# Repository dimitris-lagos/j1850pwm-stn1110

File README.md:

# j1850pwm-stn1110
OBD 2 interface with atmega328 and STN1110. Output on 16x2 LCD Screen. Implements j1850 pwm protocol.
ATMega328P fuses:
L: 0xFF
H: 0xDD
E: 0xF8
LB: 0xFD

Cad 3D Model Schematic

Prototype connected to ECU Emulator

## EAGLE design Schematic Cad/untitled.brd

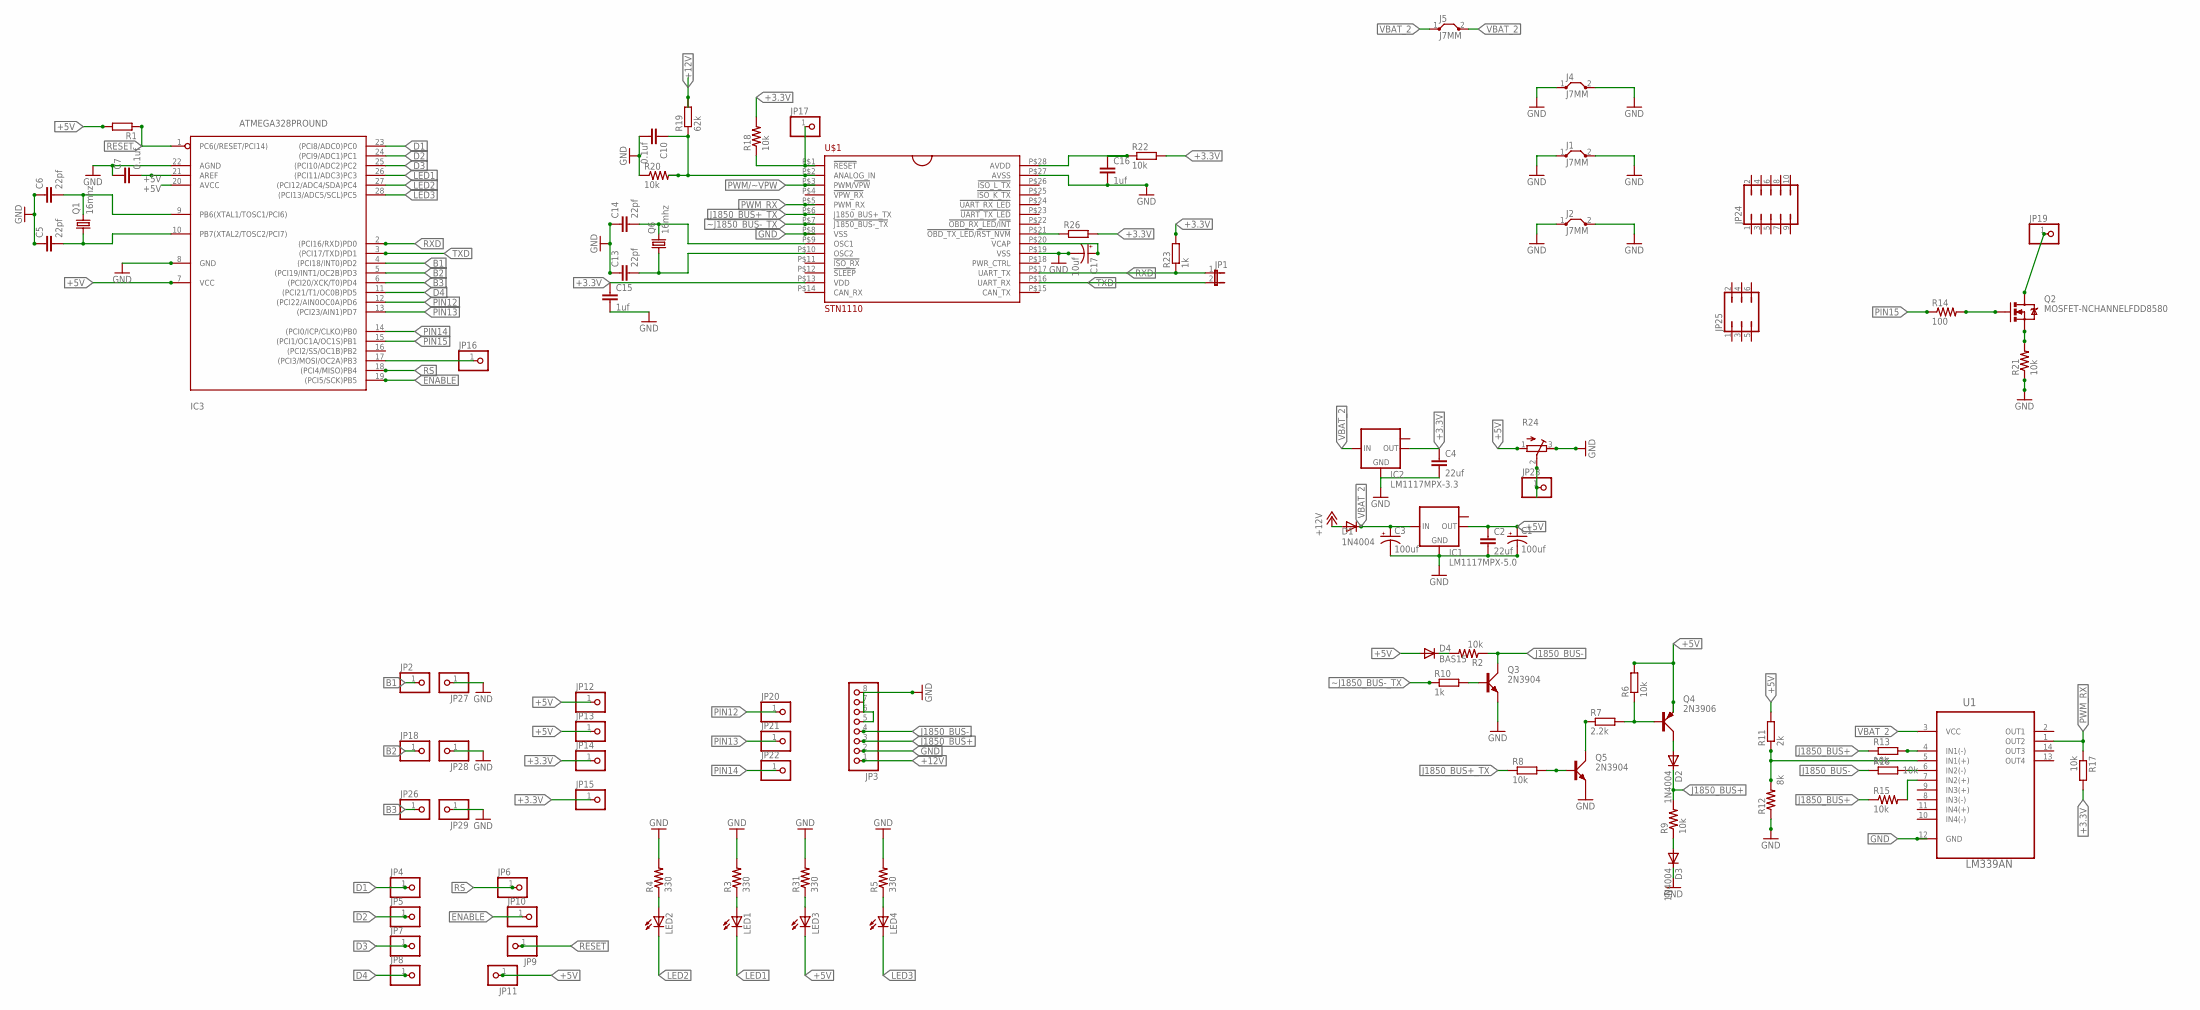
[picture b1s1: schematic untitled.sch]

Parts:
C1, C3: 100uf; CPOL-RADIAL-10UF-25V-KIT
C2, C4: 22uf; C025-025X050
C5, C6, C13, C14: 22pf; CAP-PTH-SMALL
C7: 0.1uf; C5B4.5
C10: 0.1uf; C025-025X050
C15, C16: 1uf; C025-025X050
C17: 10uf; CPOL-RADIAL-10UF-25V
D1, D2, D3: 1N4004; DO41-10
D4: BAS15; DO34-7
IC1: LM1117MPX-5.0; SOT223
IC2: LM1117MPX-3.3; SOT223
IC3: ATMEGA328PROUND; DIL28-3-ROUND
J1, J2, J4, J5: J7MM; 07
JP1: JP1E; JP1
JP2, JP4, JP5, JP6, JP7, JP8, JP9, JP10, JP11, JP12, JP13, JP14, JP15, JP16, JP17, JP18, JP19, JP20, JP21, JP22, JP23, JP26, JP27, JP28, JP29: PINHD-1X1; 1X01
JP3: PINHD-1X8; 1X08
JP24: JP5Q
JP25: JP3Q
LED1, LED2, LED4: LED3MM
LED3: LED5MM
Q1, Q6: 16mhz; HC49/S
Q2: MOSFET-NCHANNELFDD8580; DPAK
Q3, Q5: 2N3904; TO92D
Q4: 2N3906; TO92D
R1: R-EU_0207/12; 0207/12
R2, R9, R15, R20, R21: 10k; AXIAL-0.1EZ
R3, R4, R5, R31: 330; AXIAL-0.1EZ
R6, R22: 10k; 0204/7
R7: 2.2k; 0207/12
R8, R13, R16: 10k; 0207/10
R10: 1k; 0207/12
R11: 2k; 0207/10
R12: 8k; AXIAL-0.1EZ
R14: 100; AXIAL-0.1EZ
R17: 10k; 0207/12
R18: 10k; AXIAL-0.3EZ
R19: 62k; 0207/12
R23: 1k; 0207/10
R24: R-TRIMM74W; RTRIM74W
R26: R-EU_M3516; M3516
U1: LM339AN; DIP254P762X508-14
U$1: STN1110; SPDIP28

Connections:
+3.3V: C4.1, C15.1, IC2.2 (OUT), JP14.1, JP15.1, R17.2, R18.P$2 (2), R22.2, R23.2, R26.2, U$1.P$13 (VDD)
+5V: C1.1 (+), C2.1, C7.2, D4.A, IC1.2 (OUT), IC3.7 (VCC), IC3.20 (AVCC), IC3.21 (AREF), JP11.1, JP12.1, JP13.1, LED3.K (C), Q4.E, R1.2, R6.2, R11.2, R24.1 (E)
+12V: D1.A, JP3.1, R19.2
AAA: C10.1, R19.1, R20.P$2 (2), U$1.P$2 (ANALOG_IN)
B1: IC3.4 ((PCI18/INT0)PD2), JP2.1
B2: IC3.5 ((PCI19/INT1/OC2B)PD3), JP18.1
B3: IC3.6 ((PCI20/XCK/T0)PD4), JP26.1
D1: IC3.23 ((PCI8/ADC0)PC0), JP4.1
D2: IC3.24 ((PCI9/ADC1)PC1), JP5.1
D3: IC3.25 ((PCI10/ADC2)PC2), JP7.1
D4: IC3.11 ((PCI21/T1/OC0B)PD5), JP8.1
ENABLE: IC3.19 ((PCI5/SCK)PB5), JP10.1
GND: C1.2 (-), C2.2, C3.2 (-), C4.2, C5.1, C6.1, C7.1, C10.2, C13.1, C14.1, C15.2, C16.2, C17.2 (-), D3.C, IC1.1 (GND), IC2.1 (GND), IC3.8 (GND), IC3.22 (AGND), J1.1, J1.2, J2.1, J2.2, J4.1, J4.2, JP3.2, JP3.5, JP3.6, JP3.7, JP3.8, JP27.1, JP28.1, JP29.1, Q3.E, Q5.E, R3.P$2 (2), R4.P$2 (2), R5.P$2 (2), R12.P$1 (1), R20.P$1 (1), R21.P$1 (1), R24.3 (A), R31.P$2 (2), U1.12 (GND), U$1.P$8 (VSS), U$1.P$19 (VSS), U$1.P$27 (AVSS)
J1850_BUS+: D2.C, JP3.3, R9.P$2 (2), R13.1, R15.P$1 (1)
J1850_BUS+_TX: R8.1, U$1.P$6 (J1850_BUS+_TX)
J1850_BUS-: JP3.4, Q3.C, R2.P$1 (1), R16.1
LED1: IC3.26 ((PCI11/ADC3)PC3), LED1.K (C)
LED2: IC3.27 ((PCI12/ADC4/SDA)PC4), LED2.K (C)
LED3: IC3.28 ((PCI13/ADC5/SCL)PC5), LED4.K (C)
unnamed: R26.1, U$1.P$21 (!OBD_TX_LED!/!RST_NVM!)
unnamed: D4.C, R2.P$2 (2)
unnamed: Q4.B, R6.1, R7.2
unnamed: R13.2, U1.4 (IN1(-))
unnamed: Q5.C, R7.1
unnamed: D2.A, Q4.C
unnamed: Q5.B, R8.2
unnamed: Q3.B, R10.2
unnamed: D3.A, R9.P$1 (1)
unnamed: R15.P$2 (2), U1.7 (IN2(+))
unnamed: C16.1, R22.1, U$1.P$28 (AVDD)
unnamed: R16.2, U1.6 (IN2(-))
unnamed: C6.2, IC3.9 (PB6(XTAL1/TOSC1/PCI6)), Q1.2
unnamed: R11.1, R12.P$2 (2), U1.5 (IN1(+))
unnamed: C5.2, IC3.10 (PB7(XTAL2/TOSC2/PCI7)), Q1.1
unnamed: C17.1 (+), U$1.P$20 (VCAP)
unnamed: C14.2, Q6.2, U$1.P$9 (OSC1)
unnamed: C13.2, Q6.1, U$1.P$10 (OSC2)
unnamed: LED3.A, R31.P$1 (1)
unnamed: LED1.A, R3.P$1 (1)
unnamed: JP17.1, R18.P$1 (1), U$1.P$1 (!RESET!)
unnamed: LED2.A, R4.P$1 (1)
unnamed: LED4.A, R5.P$1 (1)
unnamed: IC3.17 ((PCI3/MOSI/OC2A)PB3), JP16.1
unnamed: Q2.1 (G), R14.P$2 (2)
unnamed: Q2.3 (S), R21.P$2 (2)
unnamed: JP23.1, R24.2 (S)
unnamed: JP19.1, Q2.4 (D)
PIN12: IC3.12 ((PCI22/AIN0OC0A)PD6), JP20.1
PIN13: IC3.13 ((PCI23/AIN1)PD7), JP21.1
PIN14: IC3.14 ((PCI0/ICP/CLKO)PB0), JP22.1
PIN15: IC3.15 ((PCI1/OC1A/OC1S)PB1), R14.P$1 (1)
PWM/~VPW: U$1.P$3 (PWM/!VPW!)
PWM_RX: R17.1, U1.1 (OUT2), U$1.P$5 (PWM_RX)
RESET: IC3.1 (PC6(/RESET/PCI14)), JP9.1, R1.1
RS: IC3.18 ((PCI4/MISO)PB4), JP6.1
RXD: IC3.2 ((PCI16/RXD)PD0), JP1.1, R23.1, U$1.P$17 (UART_TX)
TXD: IC3.3 ((PCI17/TXD)PD1), JP1.2, U$1.P$16 (UART_RX)
VBAT_2: C3.1 (+), D1.C, IC1.3 (IN), IC2.3 (IN), J5.1, J5.2, U1.3 (VCC)
~J1850_BUS-_TX: R10.1, U$1.P$7 (!J1850_BUS-_TX!)

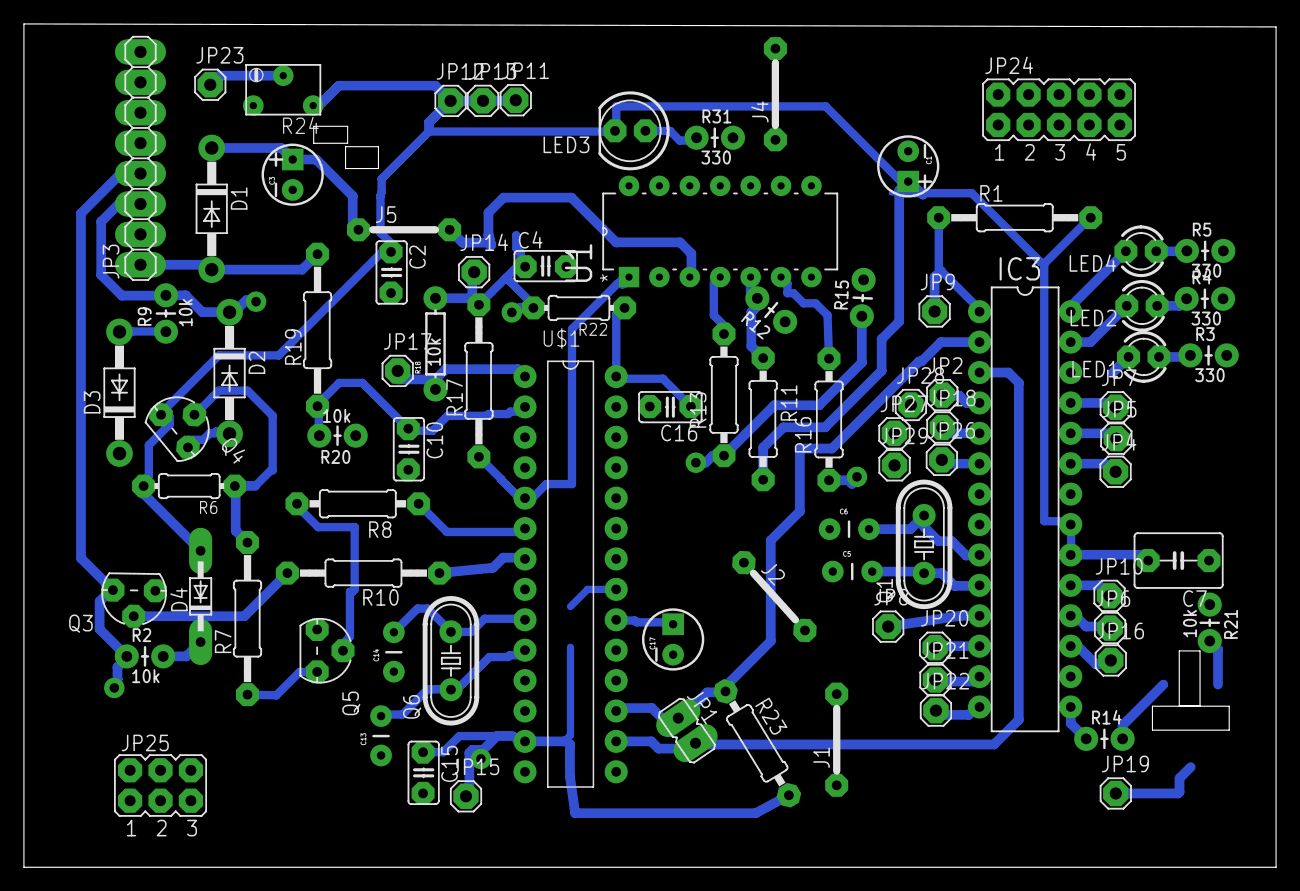
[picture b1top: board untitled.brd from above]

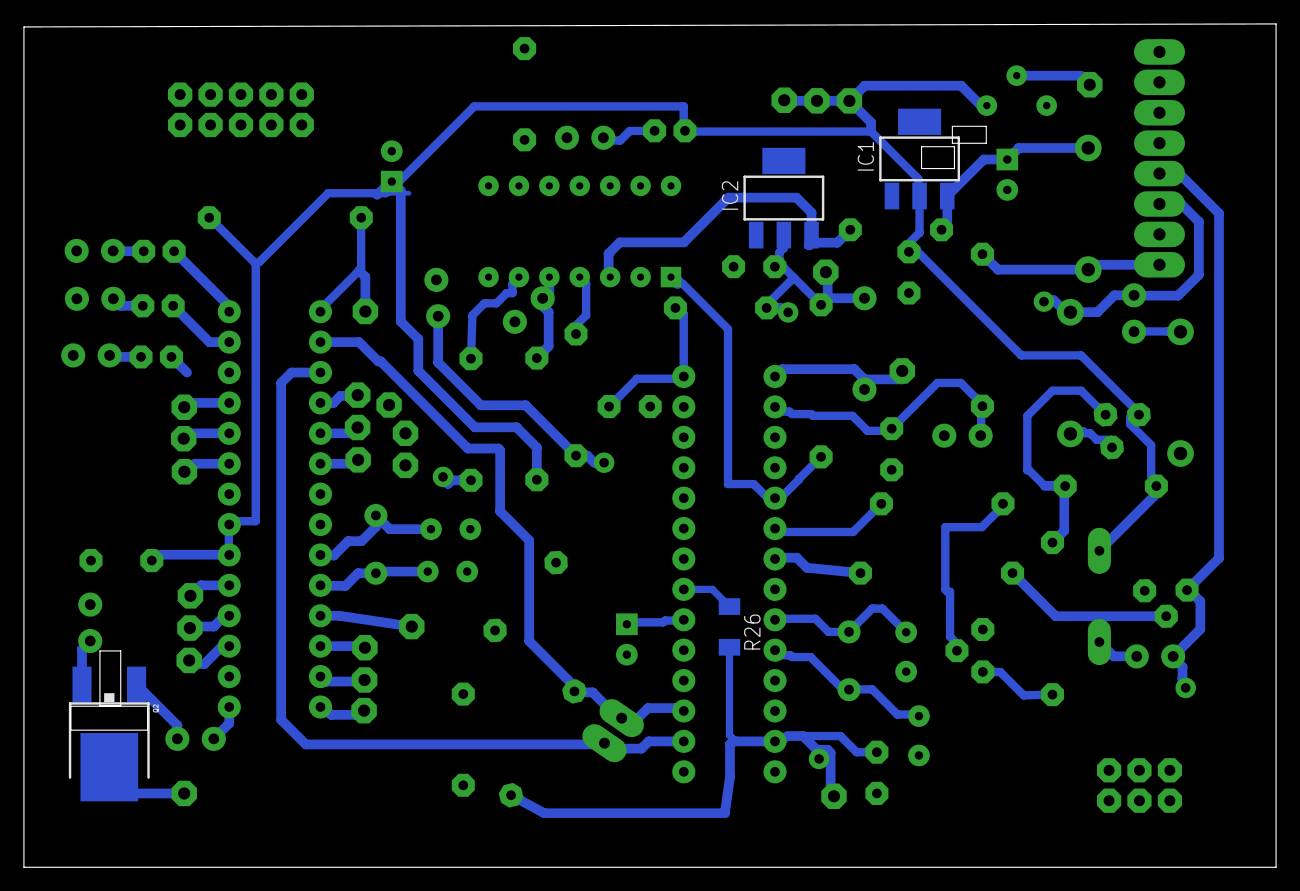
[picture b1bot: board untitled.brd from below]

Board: 2 copper layers, 104.6 x 70.5 mm, 91 parts (4 on the bottom side), 58 nets.

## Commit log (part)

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2020-05-29 Add files via upload
    -Code Update-
    Fix DTC's not reading correctly when MIL off
    Add Ventilator Relay control from setting a threshold temperature.
2020-05-29 Create LICENSE
2021-11-08 Update full_code.ino
    added comment
2021-11-08 Update full_code.ino
    typo correction
2022-07-31 code refactor
    Code refactor so that the project can be built using Visual Studio Code and Arduino CLI
2022-08-01 Added Project Cad Files
2022-08-19 Button Debounce Fix
2022-08-21 DTC reading changes
2022-08-21 removed useless files

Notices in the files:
parts and their libraries:
SparkFun-Resistors: Licensing: Creative Commons ShareAlike 4.0 International - https://creativecommons.org/licenses/by-sa/4.0
